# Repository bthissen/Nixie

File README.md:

# Nixie

This is the control program for a Nixie Clock using an ATMEGA 328p uC coupled with a DS3231M RTC to maintain and read-back the time
to IN-12B Nixie Tubes and signal with INS-1 Neon indicators (for AM/PM and colon blink). Code is in C and pre-compiled with necessary
.hex to flash directly if needed (need USBASP programmer with ICSP protocol).

Also incluced are KiCAD schematic and PCB files for editing if desired and compiled gerber files for PCB manufacured if wanted. (note: circuit
uses a CD74HC4514 4-to-16 mux to drive the nixie tubes.

#v1.0 initial publish of working model and PCB (currently not using twi.c or twi.h; plan to incorporate for ease of use for TWI protocol
#v1.5 incorporated twi.c and twi.h files for (I2C) implementation (and future modularity); also added 12hr/24hr toggle mode for UI

USAGE:
clock display using 4 nixie tubes arranged as hour(10's) | hour(1's) | minute(10's) | minute(1's) with blinking ':' indicator and 'PM' neon light represent
time over 12 hours (12hr mode only).

Time Setting:
two buttons (set and increment) are used to allow for user program of time and mode. If set button not pressed, increment button acts as toggle mode 
which will switch display from 12 hour to 24 hour and vice-versa.

to set time, press set button once (colon indicator will freeze) and select minutes with increment button to cycle minutes from 0 to 59. Once minutes is decided 
press set button again to increment hours using same increment button (1 to 12 in 12 hr mode; 0 to 24 in 24hr mode). Once hours is selected press set button for 
final time to program time. If done correctly displayed time will be written to DS3231 RTC and colon indicator will begin to blink again.

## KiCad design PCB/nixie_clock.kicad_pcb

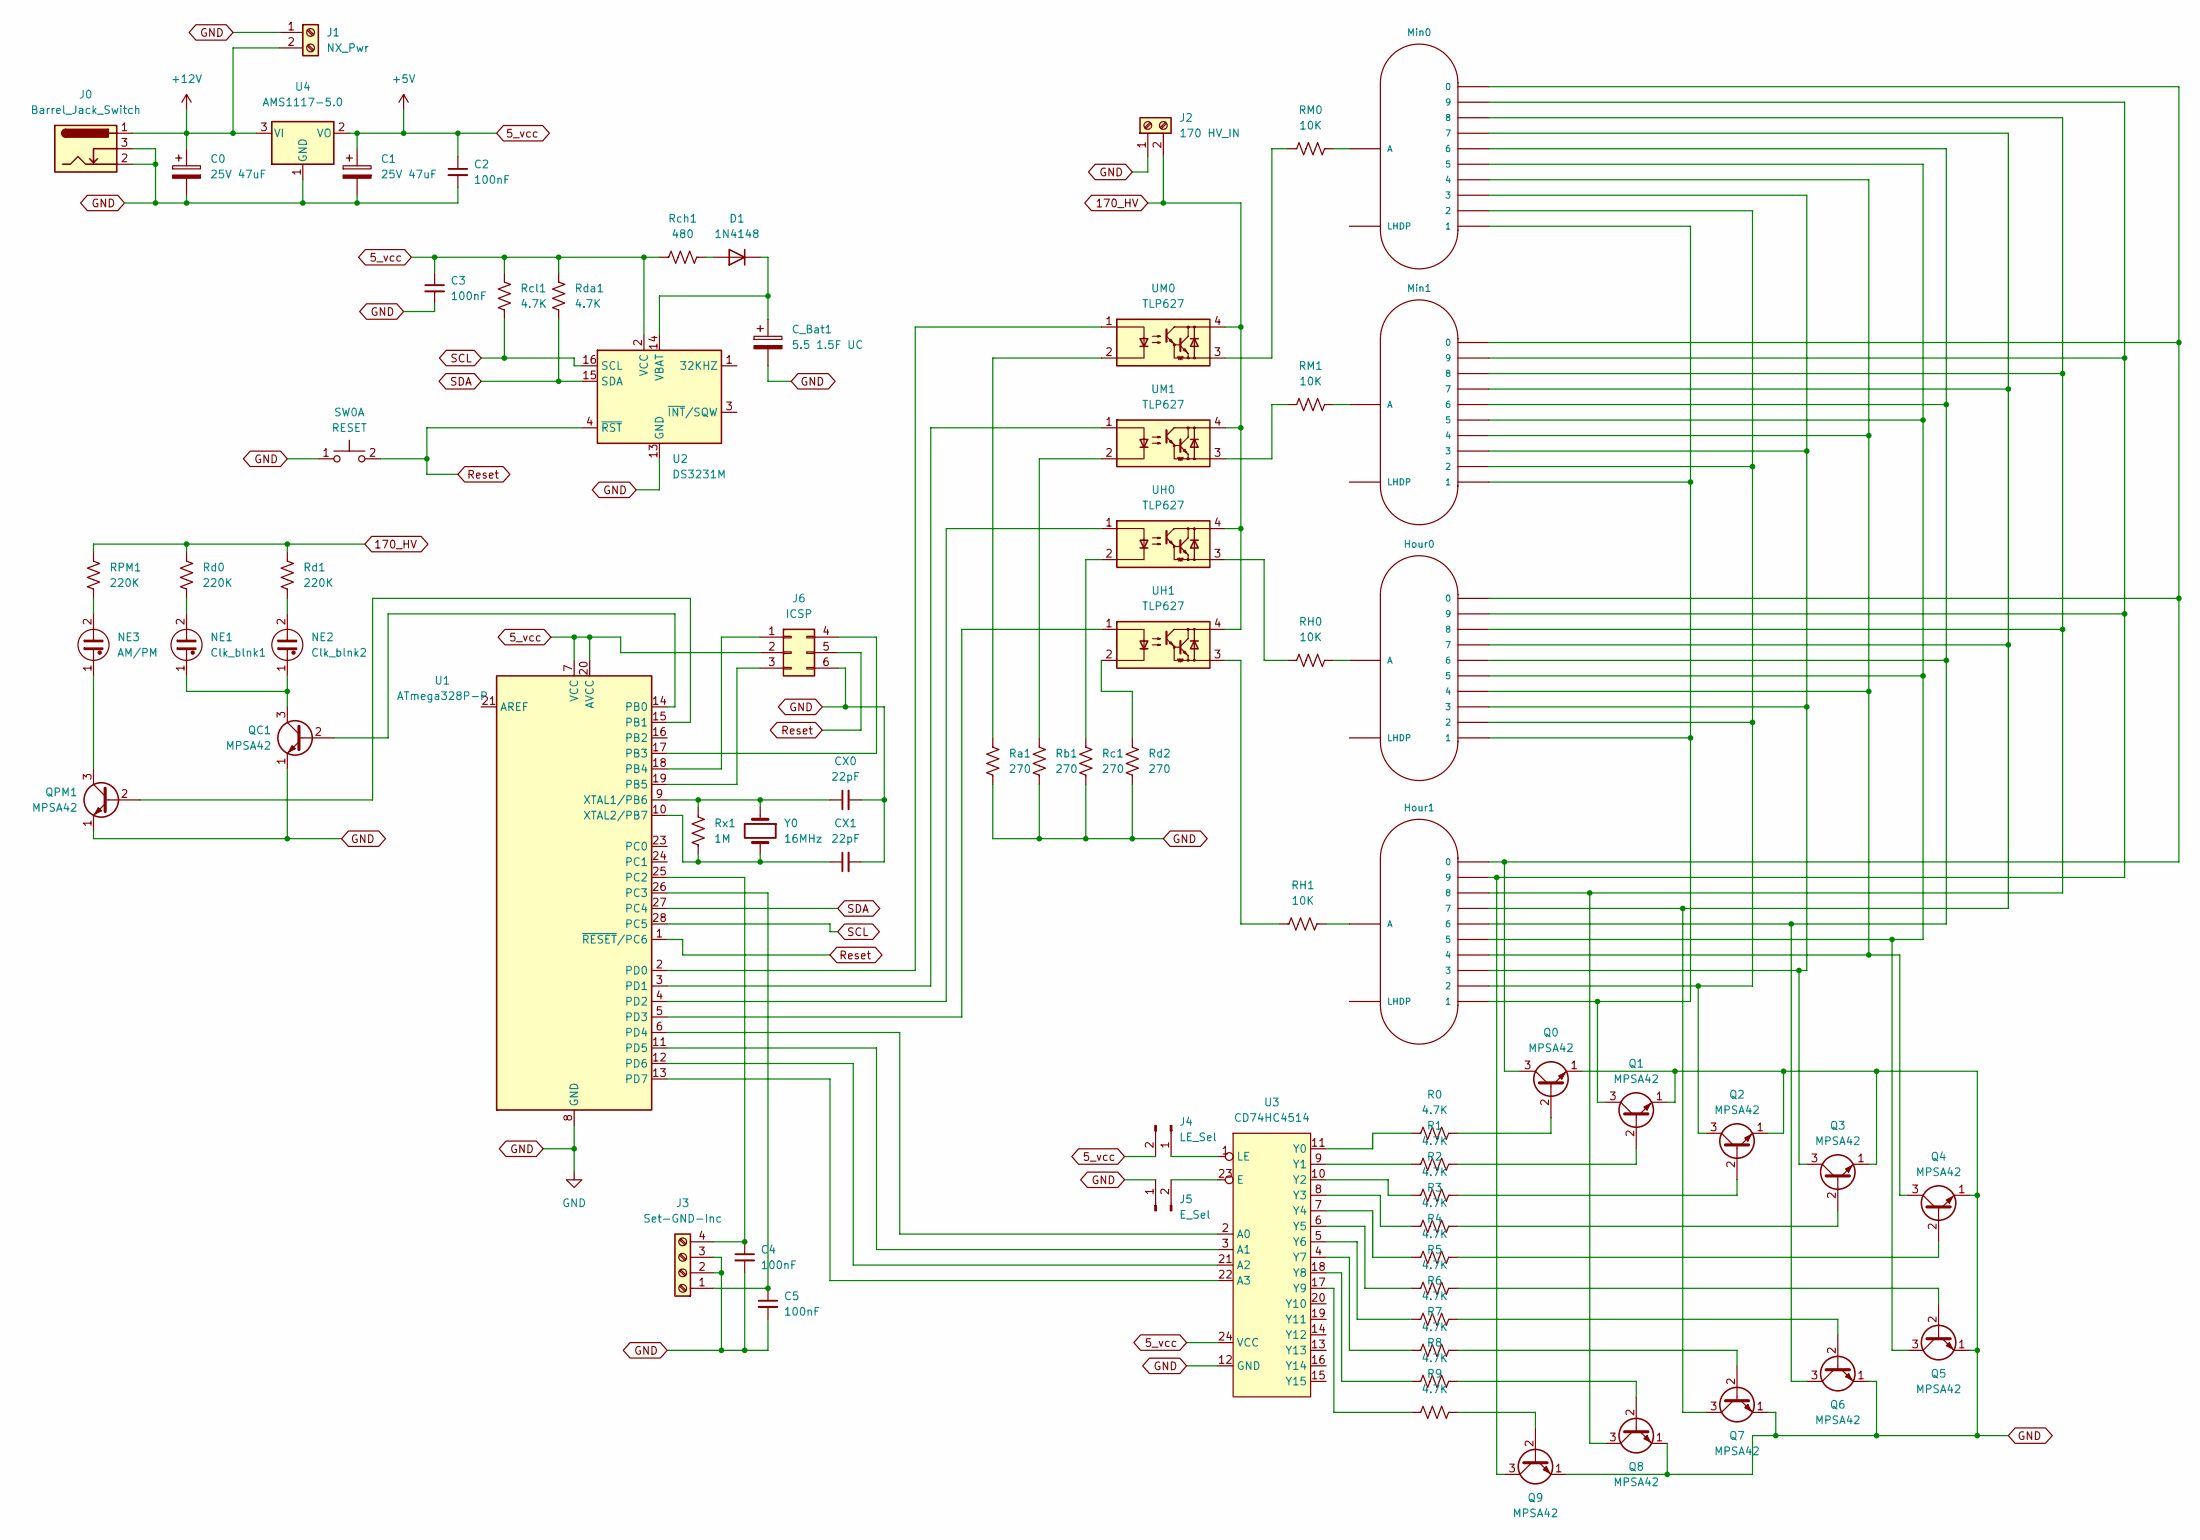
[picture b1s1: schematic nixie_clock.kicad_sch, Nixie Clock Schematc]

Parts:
C0, C1: 25V 47uF; CP_Elec_6.3x5.9
C2, C3, C4, C5: 100nF; C_Disc_D3.0mm_W2.0mm_P2.50mm
CX0, CX1: 22pF; C_Disc_D3.0mm_W2.0mm_P2.50mm
C_Bat1: 5.5 1.5F UC; DX_5R5VxxxxU_D19.0mm_P5.00mm
D1: 1N4148; D_DO-35_SOD27_P7.62mm_Horizontal
Hour0, Hour1: IN-12BORIGINAL; IN-12
J0: Barrel_Jack_Switch; BarrelJack_Horizontal
J1: NX_Pwr; TerminalBlock_TE_282834-2_1x02_P2.54mm_Horizontal
J2: 170 HV_IN; TerminalBlock_TE_282834-2_1x02_P2.54mm_Horizontal
J3: Set-GND-Inc; TerminalBlock_TE_282834-4_1x04_P2.54mm_Horizontal
J4: LE_Sel; PinHeader_1x02_P2.54mm_Vertical
J5: E_Sel; PinHeader_1x02_P2.54mm_Vertical
J6: ICSP; PinHeader_2x03_P2.54mm_Vertical
Min0, Min1: IN-12BORIGINAL; IN-12
NE1: Clk_blnk1; CP_Radial_Tantal_D6.0mm_P5.00mm
NE2: Clk_blnk2; CP_Radial_Tantal_D6.0mm_P5.00mm
NE3: AM/PM; CP_Radial_Tantal_D6.0mm_P5.00mm
Q0, Q1, Q2, Q3, Q4, Q5, Q6, Q7, Q8, Q9: MPSA42; TO-92_Inline
QC1: MPSA42; TO-92_Inline
QPM1: MPSA42; TO-92_Inline
R0, R1, R2, R3, R4, R5, R6, R7, R8, R9: 4.7K; R_Axial_DIN0207_L6.3mm_D2.5mm_P2.54mm_Vertical
RH0, RH1: 10K; R_Axial_DIN0207_L6.3mm_D2.5mm_P2.54mm_Vertical
RM0, RM1: 10K; R_Axial_DIN0207_L6.3mm_D2.5mm_P2.54mm_Vertical
RPM1: 220K; R_Axial_DIN0207_L6.3mm_D2.5mm_P2.54mm_Vertical
Ra1: 270; R_Axial_DIN0207_L6.3mm_D2.5mm_P2.54mm_Vertical
Rb1: 270; R_Axial_DIN0207_L6.3mm_D2.5mm_P2.54mm_Vertical
Rc1: 270; R_Axial_DIN0207_L6.3mm_D2.5mm_P2.54mm_Vertical
Rch1: 480; R_Axial_DIN0207_L6.3mm_D2.5mm_P2.54mm_Vertical
Rcl1: 4.7K; R_Axial_DIN0207_L6.3mm_D2.5mm_P2.54mm_Vertical
Rd0, Rd1: 220K; R_Axial_DIN0207_L6.3mm_D2.5mm_P2.54mm_Vertical
Rd2: 270; R_Axial_DIN0207_L6.3mm_D2.5mm_P2.54mm_Vertical
Rda1: 4.7K; R_Axial_DIN0207_L6.3mm_D2.5mm_P2.54mm_Vertical
Rx1: 1M; R_Axial_DIN0207_L6.3mm_D2.5mm_P2.54mm_Vertical
SW0: RESET; SW_PUSH_6mm_H7.3mm
U1: ATmega328P-P; DIP-28_W7.62mm
U2: DS3231M; SOIC-16W_7.5x10.3mm_P1.27mm
U3: CD74HC4514; SOIC-24
U4: AMS1117-5.0; SOT-223-3_TabPin2
UH0, UH1: TLP627; DIP-4_W7.62mm
UM0, UM1: TLP627; DIP-4_W7.62mm
Y0: 16MHz; Crystal_HC49-4H_Vertical

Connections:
5_vcc: C1.1, C2.1, C3.1, J4.2, J6.2, Rch1.2, Rcl1.2, Rda1.2, U1.7 (VCC), U1.20 (AVCC), U2.2 (VCC), U3.24 (VCC), U4.2 (VO)
170_HV: J2.2, RPM1.2, Rd0.2, Rd1.2, UH0.4, UH1.4, UM0.4, UM1.4
+12V: C0.1, J0.1, J1.2, U4.3 (VI)
GND: C0.2, C1.2, C2.2, C3.2, C4.2, C5.2, CX0.2, CX1.2, C_Bat1.2, J0.2, J0.3, J1.1, J2.1, J3.2, J3.3, J5.1, J6.6, Q0.1 (E), Q1.1 (E), Q2.1 (E), Q3.1 (E), Q4.1 (E), Q5.1 (E), Q6.1 (E), Q7.1 (E), Q8.1 (E), Q9.1 (E), QC1.1 (E), QPM1.1 (E), Ra1.1, Rb1.1, Rc1.1, Rd2.1, SW0.1 (C), U1.8 (GND), U1.22 (GND), U2.5 (GND), U2.6 (GND), U2.7 (GND), U2.8 (GND), U2.9 (GND), U2.10 (GND), U2.11 (GND), U2.12 (GND), U2.13 (GND), U3.12 (GND), U4.1 (GND)
unnamed: C_Bat1.1, D1.1 (K), U2.14 (VBAT)
unnamed: D1.2 (A), Rch1.1
unnamed: Hour0.A, RH0.2
unnamed: Hour0.0, Hour1.0, Min0.0, Min1.0, Q0.3 (C)
unnamed: Hour0.1, Hour1.1, Min0.1, Min1.1, Q1.3 (C)
unnamed: Hour0.2, Hour1.2, Min0.2, Min1.2, Q2.3 (C)
unnamed: Hour0.3, Hour1.3, Min0.3, Min1.3, Q3.3 (C)
unnamed: Hour0.4, Hour1.4, Min0.4, Min1.4, Q4.3 (C)
unnamed: Hour0.5, Hour1.5, Min0.5, Min1.5, Q5.3 (C)
unnamed: Hour0.6, Hour1.6, Min0.6, Min1.6, Q6.3 (C)
unnamed: Hour0.7, Hour1.7, Min0.7, Min1.7, Q7.3 (C)
unnamed: Hour0.8, Hour1.8, Min0.8, Min1.8, Q8.3 (C)
unnamed: Hour0.9, Hour1.9, Min0.9, Min1.9, Q9.3 (C)
unnamed: Hour1.A, RH1.2
unnamed: C5.1, J3.1, U1.26 (PC3)
unnamed: J4.1, U3.1 (LE)
unnamed: J5.2, U3.23 (E)
unnamed: J6.1, U1.18 (PB4)
unnamed: J6.3, U1.19 (PB5)
unnamed: J6.4, U1.17 (PB3)
unnamed: Min0.A, RM0.2
unnamed: Min1.A, RM1.2
unnamed: NE1.1, NE2.1, QC1.3 (C)
unnamed: NE1.2, Rd0.1
unnamed: NE2.2, Rd1.1
unnamed: NE3.1, QPM1.3 (C)
unnamed: NE3.2, RPM1.1
unnamed: Q0.2 (B), R0.2
unnamed: Q1.2 (B), R1.2
unnamed: Q2.2 (B), R2.2
unnamed: Q3.2 (B), R3.2
unnamed: Q4.2 (B), R4.2
unnamed: Q5.2 (B), R5.2
unnamed: Q6.2 (B), R6.2
unnamed: Q7.2 (B), R7.2
unnamed: Q8.2 (B), R8.2
unnamed: Q9.2 (B), R9.2
unnamed: QC1.2 (B), U1.14 (PB0)
unnamed: QPM1.2 (B), U1.15 (PB1)
unnamed: RH0.1, UH0.3
unnamed: RH1.1, UH1.3
unnamed: RM0.1, UM0.3
unnamed: RM1.1, UM1.3
unnamed: Ra1.2, UM0.2
unnamed: Rb1.2, UM1.2
unnamed: Rc1.2, UH0.2
unnamed: Rd2.2, UH1.2
unnamed: U1.2 (PD0), UM0.1
unnamed: U1.3 (PD1), UM1.1
unnamed: U1.4 (PD2), UH0.1
unnamed: U1.5 (PD3), UH1.1
unnamed: U1.6 (PD4), U3.2 (A0)
unnamed: CX0.1, Rx1.2, U1.9 (XTAL1/PB6), Y0.1
unnamed: CX1.1, Rx1.1, U1.10 (XTAL2/PB7), Y0.2
unnamed: U1.11 (PD5), U3.3 (A1)
unnamed: U1.12 (PD6), U3.21 (A2)
unnamed: U1.13 (PD7), U3.22 (A3)
unnamed: C4.1, J3.4, U1.25 (PC2)
unnamed: R7.1, U3.4 (Y7)
unnamed: R6.1, U3.5 (Y6)
unnamed: R5.1, U3.6 (Y5)
unnamed: R4.1, U3.7 (Y4)
unnamed: R3.1, U3.8 (Y3)
unnamed: R1.1, U3.9 (Y1)
unnamed: R2.1, U3.10 (Y2)
unnamed: R0.1, U3.11 (Y0)
unnamed: R9.1, U3.17 (Y9)
unnamed: R8.1, U3.18 (Y8)
Reset: J6.5, SW0.2 (D), U1.1 (~RESET/PC6), U2.4 (~RST)
SCL: Rcl1.1, U1.28 (PC5), U2.16 (SCL)
SDA: Rda1.1, U1.27 (PC4), U2.15 (SDA)

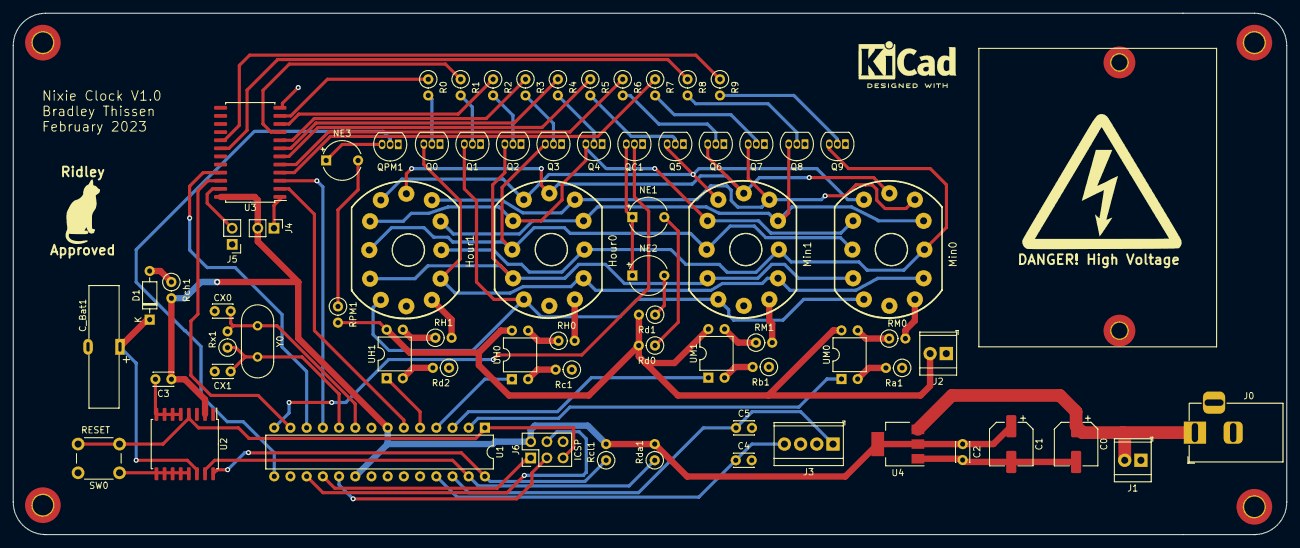
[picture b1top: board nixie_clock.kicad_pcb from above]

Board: 2 copper layers, 199.6 x 81.7 mm, 73 parts (0 on the bottom side), 75 nets.

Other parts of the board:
DANGER! High Voltage: LOGO; HVbmp25
Ridley: LOGO; cat10

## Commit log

2023-03-06 Initial commit of Nixie Clock Files to Github with working basic functionality (added compiled files for direct programming of ATMEGA 328p if desired)
    Also added PCB with gerber files and raw KiCAD files for editing or
    re-production if desired
2023-03-06 test
2023-03-06 Added reference images
2023-03-09 incorporated twi.c/h and added toggle mode
2023-03-09 final revision to retain time on reset
2023-03-09 Update README.md
    updated with v1.5 changes and usage instructions
